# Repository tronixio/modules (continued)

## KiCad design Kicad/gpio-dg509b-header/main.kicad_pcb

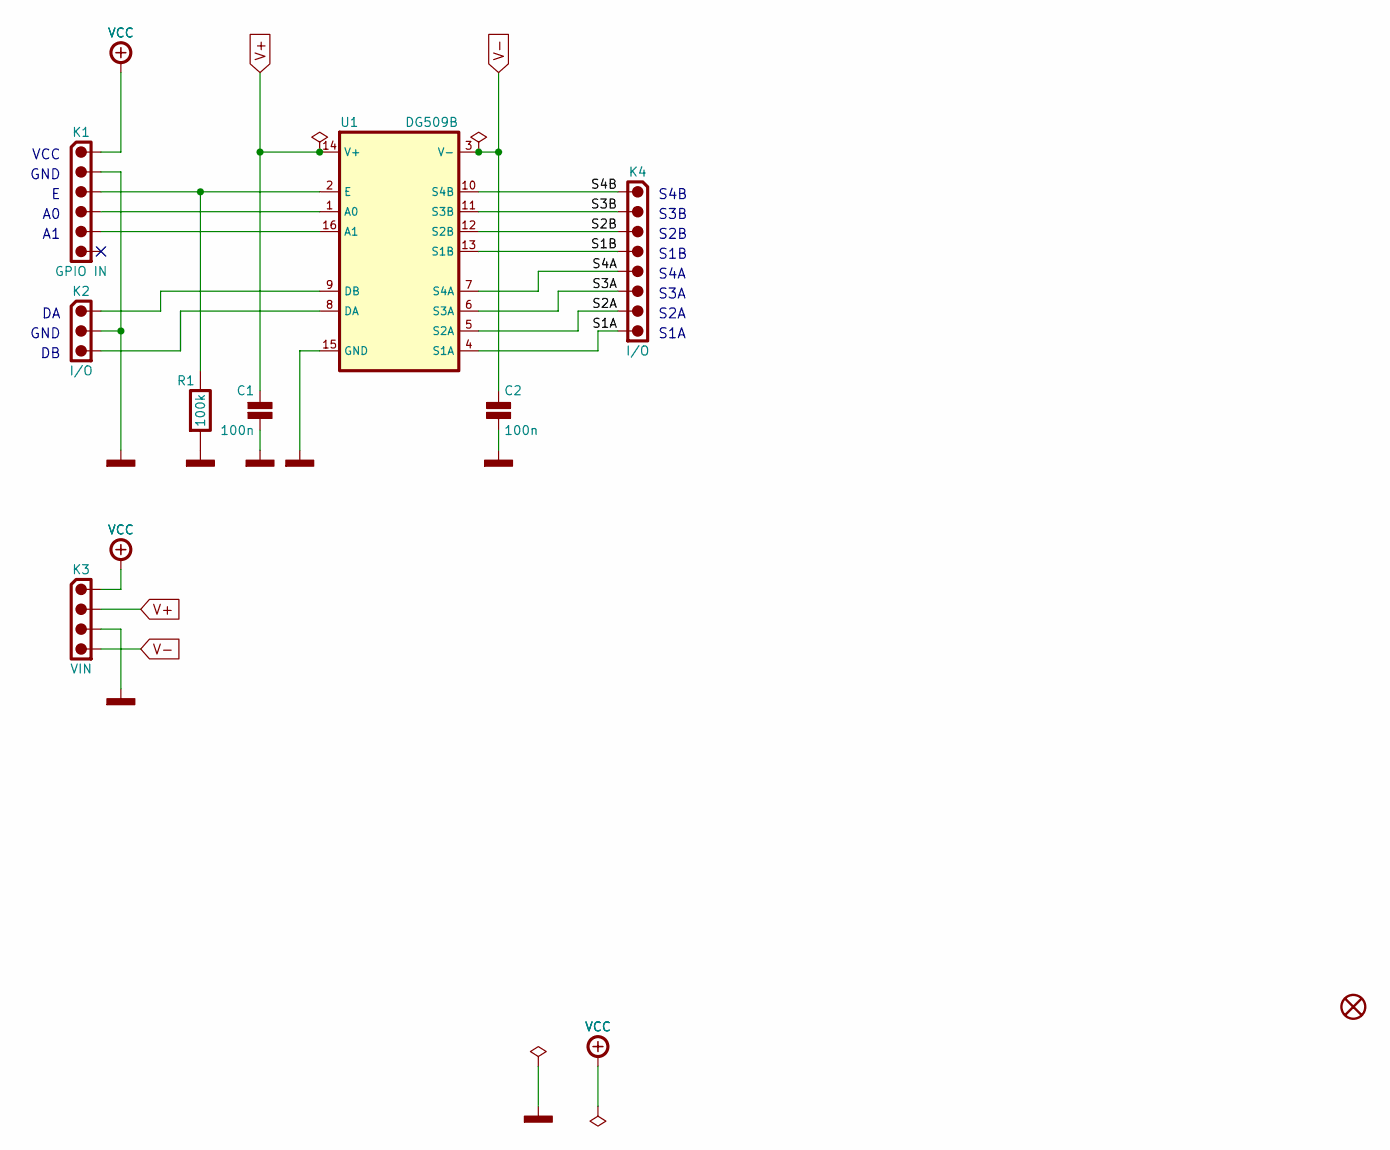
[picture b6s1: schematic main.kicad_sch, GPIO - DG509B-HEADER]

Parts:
C1, C2: 100n; CAPACITOR-SMD-1206; Voltage 50V; Tolerance 5%; Mouser 80-C1206C104J5R
K1: GPIO IN; HARWIN-M20-975064x; Mouser 855-M20-975064
K2: I/O; HARWIN-M20-999034x; Mouser 855-M20-999034
K3: VIN; HARWIN-M20-999044x; Mouser 855-M20-999044
K4: I/O; HARWIN-M20-999084x; Mouser 855-M20-999084
R1: 100k; RESISTOR-SMD-1206; Tolerance 5%; Mouser 660-RK73B2BTTDD104J
U1: DG509B; SOIC-16; Mouser 781-DG509BEY-E3
U2: 3M-SJ5376; Mouser 517-SJ5376

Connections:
/S1A: K4.8, U1.4 (S1A)
/S1B: K4.4, U1.13 (S1B)
/S2A: K4.7, U1.5 (S2A)
/S2B: K4.3, U1.12 (S2B)
/S3A: K4.6, U1.6 (S3A)
/S3B: K4.2, U1.11 (S3B)
/S4A: K4.5, U1.7 (S4A)
/S4B: K4.1, U1.10 (S4B)
unnamed: K1.4, U1.1 (A0)
unnamed: K1.5, U1.16 (A1)
unnamed: K2.3, U1.8 (DA)
unnamed: K2.1, U1.9 (DB)
unnamed: K1.3, R1.1, U1.2 (E)
POWER-+VCC: K1.1, K3.1
POWER-GND: C1.2, C2.2, K1.2, K2.2, K3.3, R1.2, U1.15 (GND)
V+: C1.1, K3.2, U1.14 (V+)
V-: C2.1, K3.4, U1.3 (V-)

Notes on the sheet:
S4B
S2B
S3A
VCC
S1A
S2A
S3B
GND
S1B
S4A

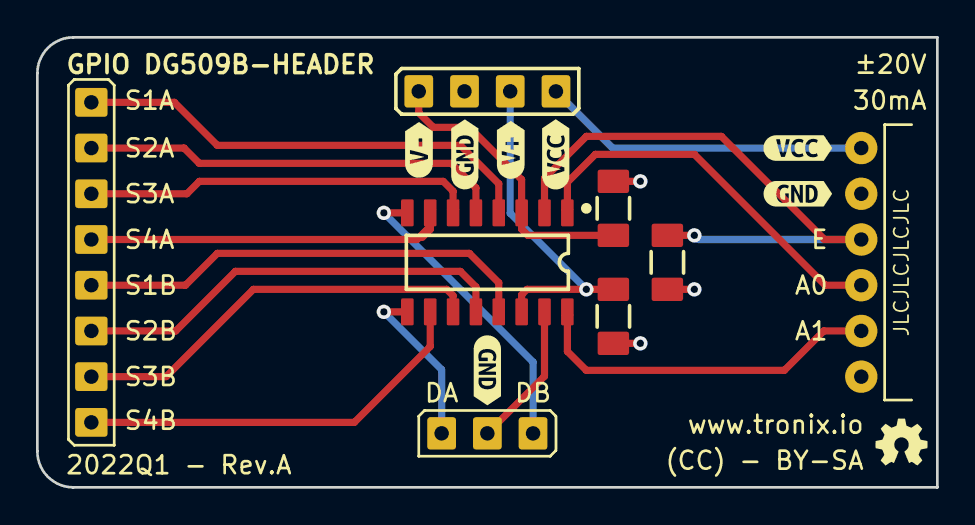
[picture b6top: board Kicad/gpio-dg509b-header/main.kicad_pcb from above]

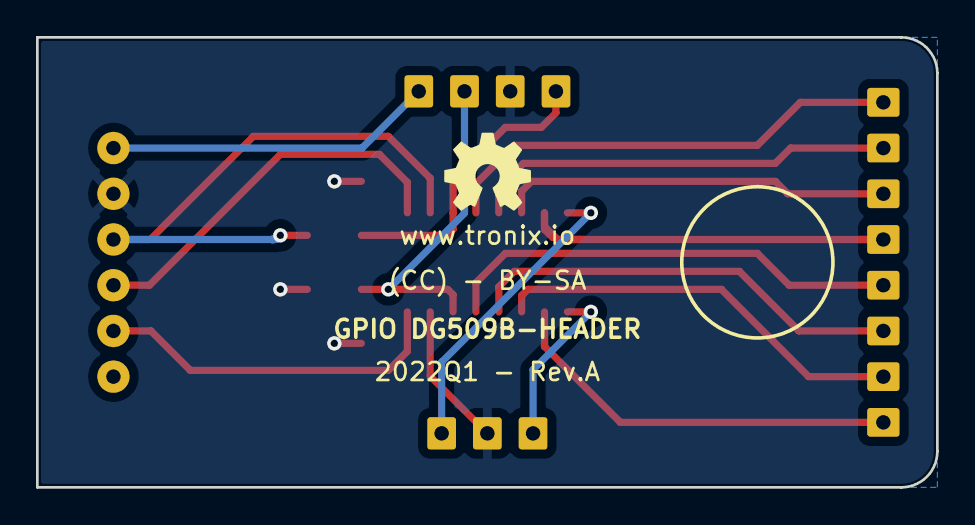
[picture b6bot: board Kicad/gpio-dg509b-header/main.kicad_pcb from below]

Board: 2 copper layers, 50.0 x 25.0 mm, 17 parts (2 on the bottom side), 17 nets.

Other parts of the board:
GT: LOGO; OSHW-5MM
kibuzzard-62B2FE3C: G***; kibuzzard-62B2FE3C
kibuzzard-62B2FE4D: G***; kibuzzard-62B2FE4D
kibuzzard-66858EC7: G***; kibuzzard-66858EC7
kibuzzard-66858EE5: G***; kibuzzard-66858EE5
kibuzzard-66858F0C: G***; kibuzzard-66858F0C
kibuzzard-66858F12: G***; kibuzzard-66858F12
kibuzzard-668593CE: G***; kibuzzard-668593CE

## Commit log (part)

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2022-06-22 74HC595
2022-06-23 Updaet
2022-09-30 Initial commit HC4053
2022-10-02 HC595 Chase
2023-01-31 GPIO BreadBoard
2024-03-17 Update Kicad 8
2024-06-26 Update Breadboard
2024-07-03 Delete
2026-05-01 GPIO HC595
2026-05-01 GPIO HC4053
